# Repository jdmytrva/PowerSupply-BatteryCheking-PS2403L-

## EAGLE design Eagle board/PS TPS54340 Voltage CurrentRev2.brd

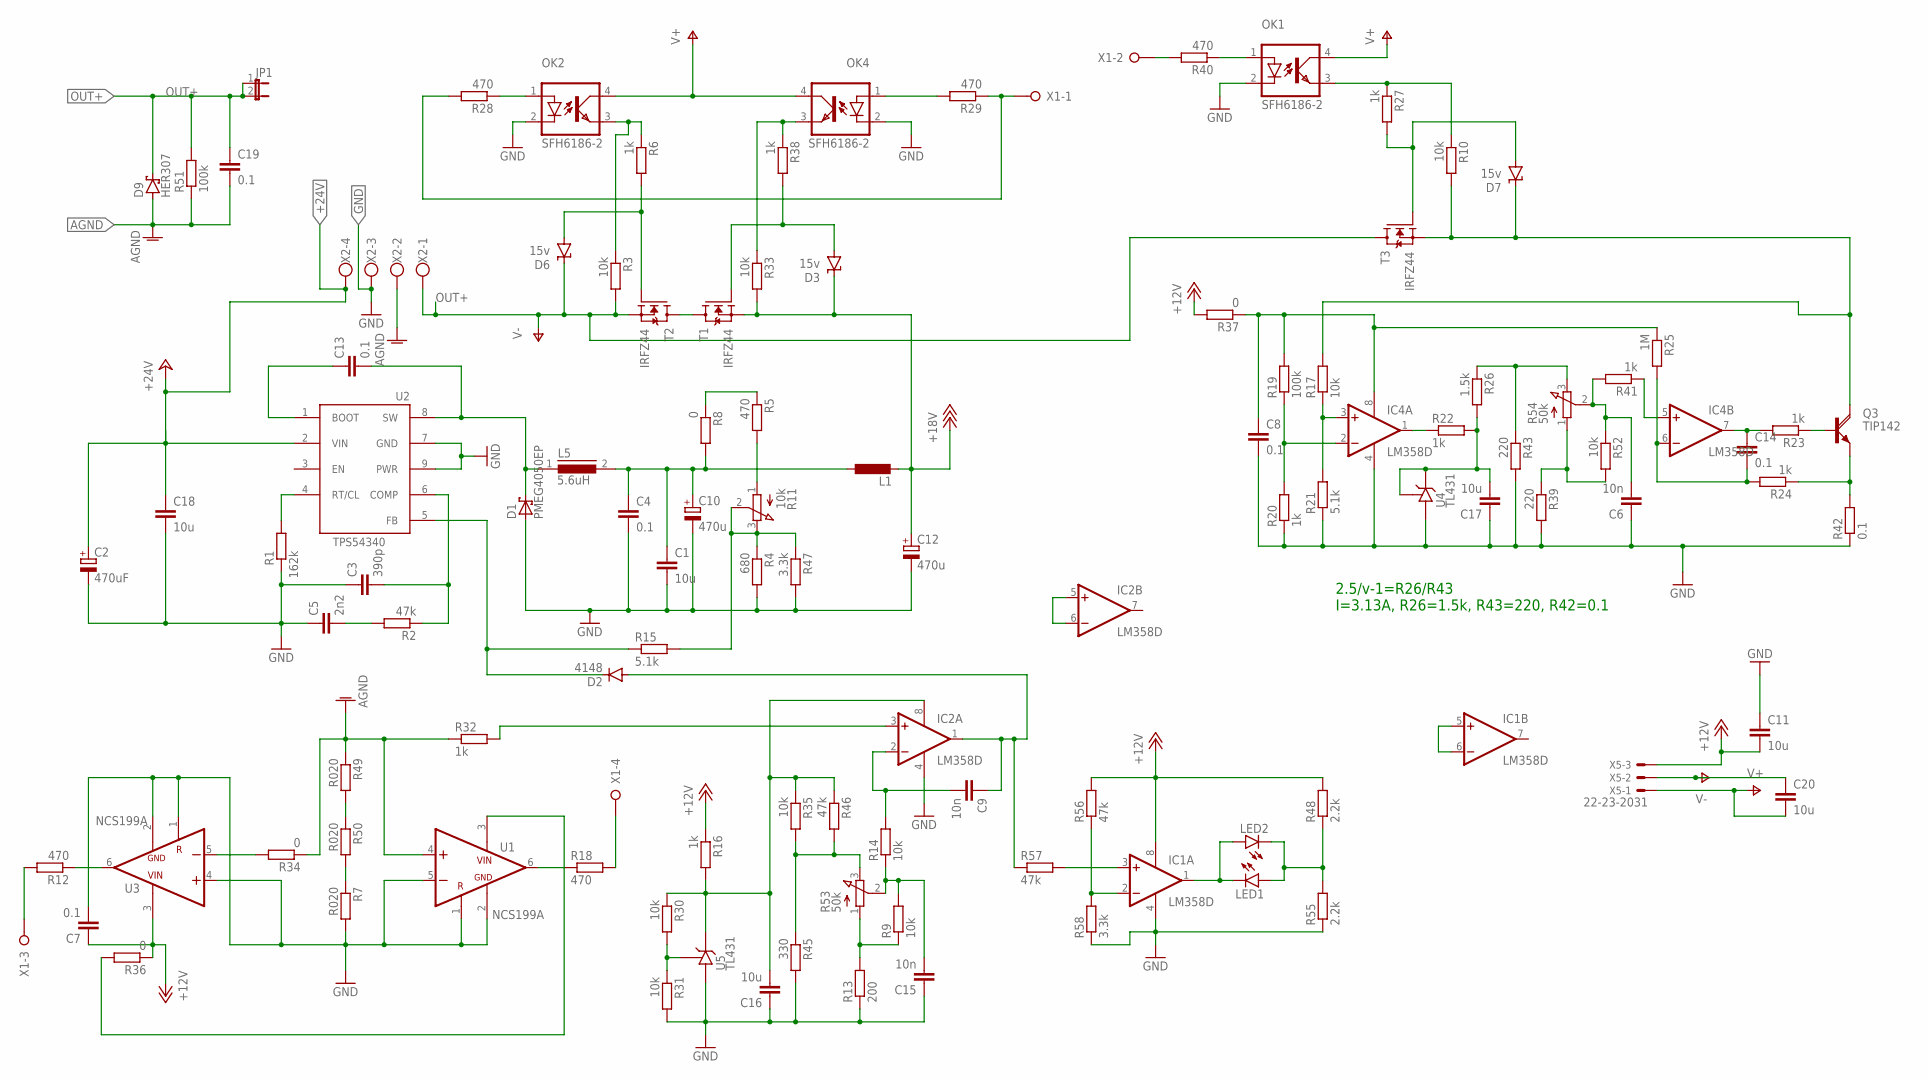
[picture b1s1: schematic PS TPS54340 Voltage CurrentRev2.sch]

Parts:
C1, C18: 10u; C1210
C2: 470uF; E5-10,5
C3: 390p; C0603K
C4, C8, C14: 0.1; C1206
C5: 2n2; C0603K
C6, C9, C15: 10n; C0603K
C7: 0.1; C0603K
C10, C12: 470u; E5-10,5
C11, C20: 10u; C1206
C13: 0.1; C102-043X133
C16, C17: 10u; C0603K
C19: 0.1; C150-054X183
D1: PMEG4050EP; SOD128
D2: 4148; SOD80C
D3, D6, D7: 15v; SMBJ
D9: HER307; CB429-17
IC1, IC2, IC4: LM358D; SO08
JP1: JP1E; JP1
L1: L-EU0207/5V; 0207/5V
L5: 5.6uH; DR125
LED1, LED2: LEDB152; Q62902-B152
OK1, OK2, OK4: SFH6186-2; SMD4-7
Q3: TIP142; SOT93
R1: 162k; R1206
R2, R46, R56, R57: 47k; R0603
R3, R9, R10, R30, R31, R33, R35, R52: 10k; R0603
R4: 680; R1206
R5: 470; R1206
R6, R16, R22, R27, R38: 1k; R0603
R7, R49, R50: R020; R1206
R8: 0; R0603
R11: 10k; 3RP/1610N
R12, R18, R28, R29, R40: 470; R0603
R13: 200; R0603
R14, R17: 10k; R1206
R15: 5.1k; R0603
R19: 100k; R1206
R20, R23, R24, R32, R41: 1k; R1206
R21: 5.1k; R1206
R25: 1M; R1206
R26: 1.5k; R0603
R34, R36, R37: 0; R1206
R39, R43: 220; R0603
R42: 0.1; 0414/15
R45: 330; R0603
R47: 3.3k; R1206
R48, R55: 2.2k; R0603
R51: 100k; 0207/15
R53, R54: 50k; 3RP/1610N
R58: 3.3k; R0603
T1, T2, T3: IRFZ44; DPAK_TO252
U1, U3: NCS199A; SOT363
U2: TPS54340; HSOP
U4, U5: TL431; SOT23
X1: W237-04P; W237-4P
X2: W237-4
X5: 22-23-2031

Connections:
+12V: C7.1, C11.2, IC1.8 (V+), R16.1, R36.1, R37.2, R48.2, R56.2, U3.3 (VCC), X5.3
+18V: C12.+, D3.C, L1.2, R33.2, T1.3 (S)
+24V: C2.+, C18.1, U2.2 (VIN), X2.4
AGND: C19.2, D9.A, R32.1, R34.1, R49.1, R51.1, U1.4 (IN+), X2.2
GND: C1.2, C2.-, C3.1, C4.2, C5.1, C6.1, C7.2, C8.2, C10.-, C11.1, C12.-, C15.1, C16.1, C17.1, C18.2, D1.2 (A), IC1.4 (V-), IC2.4 (V-), IC4.4 (V-), OK1.2 (C), OK2.2 (C), OK4.2 (C), R1.1, R4.2, R7.2, R13.1, R20.1, R21.1, R31.2, R39.2, R42.1, R43.2, R45.2, R47.2, R55.1, R58.1, U1.1 (REF), U1.2 (GND), U1.5 (IN-), U2.7 (GND), U2.9 (PWR), U3.1 (REF), U3.2 (GND), U3.4 (IN+), U4.3 (A), U5.3 (A), X2.3
unnamed: R1.2, U2.4 (RT/CL)
unnamed: C5.2, R2.2
unnamed: C3.2, R2.1, U2.6 (COMP)
unnamed: R5.2, R11.1 (A)
unnamed: D6.A, R6.2, T2.1 (G)
unnamed: IC2.3 (+IN), R32.2
unnamed: R4.1, R11.2 (S), R11.3 (E), R15.2, R47.1
unnamed: C16.2, IC2.8 (V+), R16.2, R30.1, R35.1, R46.1, U5.1 (C)
unnamed: OK2.3 (EMIT), R3.1, R6.1
unnamed: D3.A, R38.2, T1.1 (G)
unnamed: C13.1, U2.1 (BOOT)
unnamed: C13.2, D1.1 (K), L5.1, U2.8 (SW)
unnamed: R12.1, U3.6 (OUT)
unnamed: C9.2, IC2.2 (-IN), R14.2
unnamed: R30.2, R31.1, U5.2 (R)
unnamed: C9.1, D2.A, IC2.1 (OUT), R57.1
unnamed: C15.2, R9.2, R14.1, R53.2 (S)
unnamed: R34.2, U3.5 (IN-)
unnamed: D2.C, R15.1, U2.5 (FB)
unnamed: R18.1, U1.6 (OUT)
unnamed: T1.2 (D), T2.2 (D)
unnamed: IC1.1 (OUT), LED1.K (C), LED2.A
unnamed: C1.1, C4.1, C10.+, L1.1, L5.2, R8.2
unnamed: Q3.B, R23.1
unnamed: OK1.1 (A), R40.1
unnamed: C14.2, IC4.6 (-IN), R24.2, R25.2
unnamed: R26.1, R43.1, R54.3 (E)
unnamed: D7.C, Q3.C, R10.2, R17.2, T3.3 (S)
unnamed: OK1.3 (EMIT), R10.1, R27.1
unnamed: LED1.A, LED2.K (C), R48.1, R55.2
unnamed: R35.2, R45.1, R46.2, R53.3 (E)
unnamed: IC4.5 (+IN), R41.1
unnamed: IC1.2 (-IN), R56.1, R58.2
unnamed: R36.2, U1.3 (VCC)
unnamed: R18.2, X1.4
unnamed: R12.2, X1.3
unnamed: D7.A, R27.2, T3.1 (G)
unnamed: R39.1, R52.2, R54.1 (A)
unnamed: C8.1, IC4.8 (V+), R19.2, R25.1, R37.1
unnamed: R40.2, X1.2
unnamed: R9.1, R13.2, R53.1 (A)
unnamed: R49.2, R50.1
unnamed: IC2.5 (+IN), IC2.6 (-IN)
unnamed: IC1.3 (+IN), R57.2
unnamed: IC1.5 (+IN), IC1.6 (-IN)
unnamed: R7.1, R50.2
unnamed: OK4.3 (EMIT), R33.1, R38.1
unnamed: OK4.1 (A), R29.2
unnamed: R28.2, R29.1, X1.1
unnamed: OK2.1 (A), R28.1
unnamed: C17.2, R22.2, R26.2, U4.1 (C), U4.2 (R)
unnamed: R5.1, R8.1
unnamed: Q3.E, R24.1, R42.2
unnamed: C14.1, IC4.7 (OUT), R23.2
unnamed: C6.2, R41.2, R52.1, R54.2 (S)
unnamed: IC4.1 (OUT), R22.1
unnamed: IC4.3 (+IN), R17.1, R21.2
unnamed: IC4.2 (-IN), R19.1, R20.2
OUT+: C19.1, C20.1, D6.C, D9.C, JP1.1, JP1.2, R3.2, R51.2, T2.3 (S), T3.2 (D), X2.1, X5.2
V+: C20.2, OK1.4 (COL), OK2.4 (COL), OK4.4 (COL), X5.1

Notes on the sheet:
2.5/v-1=R26/R43 I=3.13A, R26=1.5k, R43=220, R42=0.1

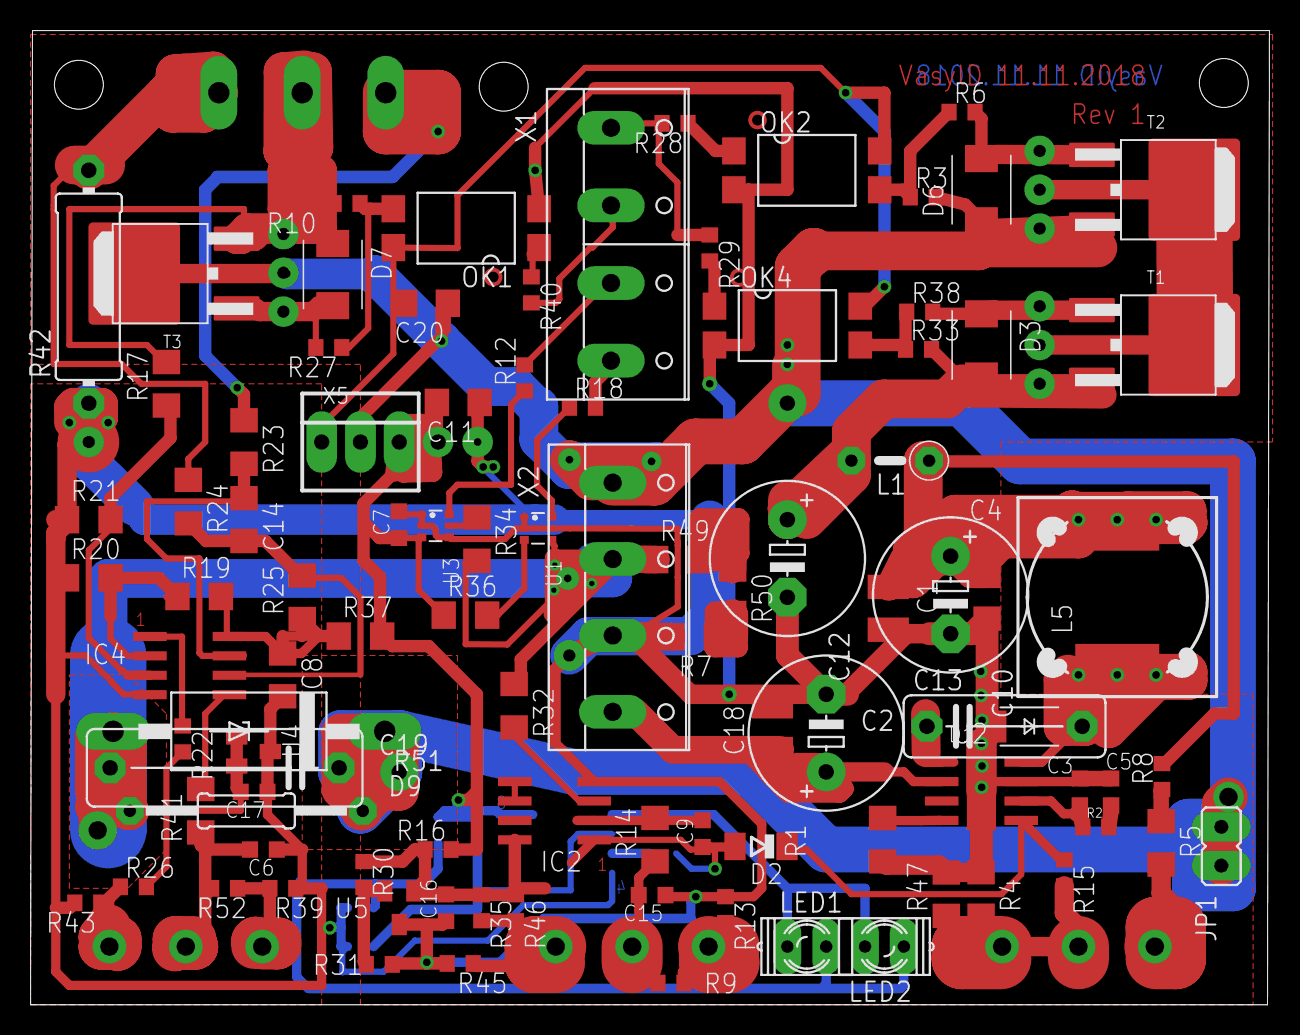
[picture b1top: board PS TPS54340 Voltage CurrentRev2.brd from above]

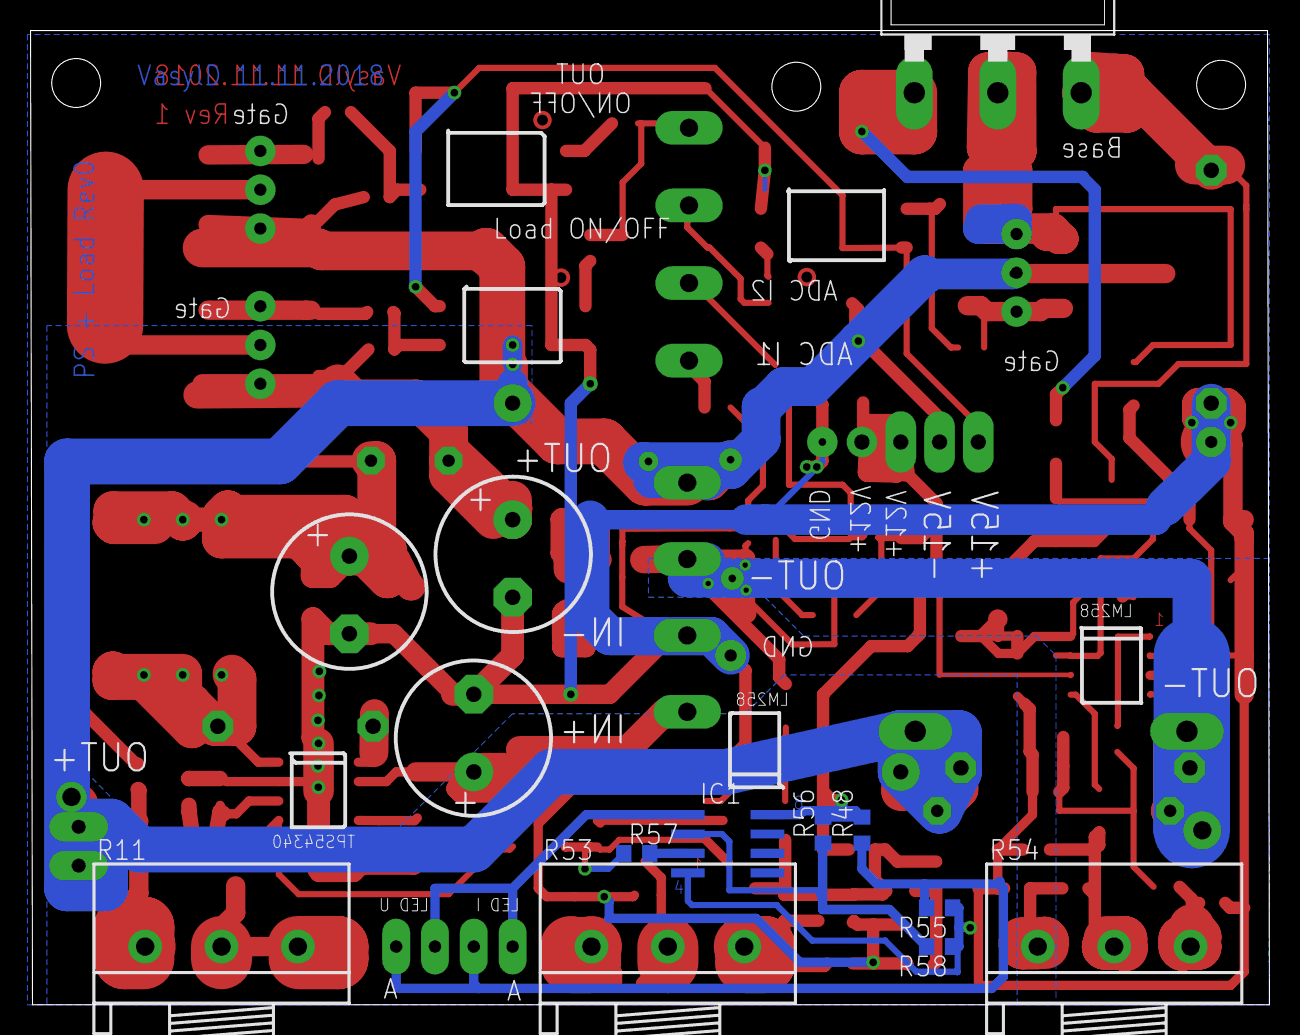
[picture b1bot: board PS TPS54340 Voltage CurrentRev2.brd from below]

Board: 2 copper layers, 81.1 x 63.8 mm, 106 parts (10 on the bottom side), 65 nets.

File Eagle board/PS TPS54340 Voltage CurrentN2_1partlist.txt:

Partlist

Exported from PS TPS54340 Voltage CurrentN2_1.sch at 15.11.2018 13:39

EAGLE Version 9.2.2 Copyright (c) 1988-2018 Autodesk, Inc.

Assembly variant: 

Part     Value          Device          Package      Library          Sheet

C1       10u            C-EUC1210       C1210        rcl              1
C2       470uF          CPOL-EUE5-10.5  E5-10,5      rcl              1
C3       47p            C-EUC0603K      C0603K       rcl              1
C4       0.1            C-EUC1206       C1206        rcl              1
C5       1n             C-EUC0603K      C0603K       rcl              1
C6       0.1            C-EUC0603K      C0603K       rcl              1
C7       0.1            C-EUC0603K      C0603K       rcl              1
C8       0.1            C-EUC1206       C1206        rcl              1
C9       10n            C-EUC0603K      C0603K       rcl              1
C10      470u           CPOL-EUE5-10.5  E5-10,5      rcl              1
C11      0.1            C-EUC1206       C1206        rcl              1
C12      470u           CPOL-EUE5-10.5  E5-10,5      rcl              1
C13      0.1            C-EU102-043X133 C102-043X133 rcl              1
C14      0.1            C-EUC1206       C1206        rcl              1
C15      0.1            C-EUC0603K      C0603K       rcl              1
C16      10u            C-EUC0603K      C0603K       rcl              1
C17      10u            C-EUC0603K      C0603K       rcl              1
C18      10u            C-EUC1210       C1210        rcl              1
C19      0.1            C-EU150-054X183 C150-054X183 rcl              1
C20      0.1            C-EUC1206       C1206        rcl              1
D1       PMEG4050EP     PMEG4050EP      SOD128       NXP_60_26022015  1
D2       4148           PMLL41SOD80C    SOD80C       diode            1
D3       15v            SUPPRESSOR-SMBJ SMBJ         diode            1
D6       15v            SUPPRESSOR-SMBJ SMBJ         diode            1
D7       15v            SUPPRESSOR-SMBJ SMBJ         diode            1
D9       HER307         15KEXX          CB429-17     diode            1
IC1      LM358D         LM358D          SO08         linear           1
IC2      LM358D         LM358D          SO08         linear           1
IC4      LM358D         LM358D          SO08         linear           1
JP1                     JP1E            JP1          jumper           1
L1                      L-EU0207/5V     0207/5V      rcl              1
L5       5.6uH          DR125           DR125        inductors        1
LED1                    LEDB152         Q62902-B152  led              1
LED2                    LEDB152         Q62902-B152  led              1
OK1      SFH6186-2      SFH6186-2       SMD4-7       optocoupler      1
OK2      SFH6186-2      SFH6186-2       SMD4-7       optocoupler      1
OK4      SFH6186-2      SFH6186-2       SMD4-7       optocoupler      1
Q3       TIP142         TIP142          SOT93        transistor-power 1
R1       150k           R-EU_R1206      R1206        rcl              1
R2       47k            R-EU_R0603      R0603        rcl              1
R3       10k            R-EU_R0603      R0603        rcl              1
R4       470            R-EU_R1206      R1206        rcl              1
R5       470            R-EU_R1206      R1206        rcl              1
R6       1k             R-EU_R0603      R0603        rcl              1
R7       R020           R-EU_R1206      R1206        rcl              1
R8       x              R-EU_R0603      R0603        rcl              1
R9       10k            R-EU_R0603      R0603        rcl              1
R10      10k            R-EU_R0603      R0603        rcl              1
R11      10k            3RP/1610N       3RP/1610N    pot              1
R12      1k             R-EU_R0603      R0603        rcl              1
R13      200            R-EU_R0603      R0603        rcl              1
R14      10k            R-EU_R1206      R1206        rcl              1
R15      5.1k           R-EU_R0603      R0603        rcl              1
R16      1k             R-EU_R0603      R0603        rcl              1
R17      10k            R-EU_R1206      R1206        rcl              1
R18      1k             R-EU_R0603      R0603        rcl              1
R19      100k           R-EU_R1206      R1206        rcl              1
R20      1k             R-EU_R1206      R1206        rcl              1
R21      5.1k           R-EU_R1206      R1206        rcl              1
R22      1k             R-EU_R0603      R0603        rcl              1
R23      1k             R-EU_R1206      R1206        rcl              1
R24      1k             R-EU_R1206      R1206        rcl              1
R25      1M             R-EU_R1206      R1206        rcl              1
R26      1.5k           R-EU_R0603      R0603        rcl              1
R27      1k             R-EU_R0603      R0603        rcl              1
R28      470            R-EU_R0603      R0603        rcl              1
R29      470            R-EU_R0603      R0603        rcl              1
R30      10k            R-EU_R0603      R0603        rcl              1
R31      10k            R-EU_R0603      R0603        rcl              1
R32      1k             R-EU_R1206      R1206        rcl              1
R33      10k            R-EU_R0603      R0603        rcl              1
R34      0              R-EU_R1206      R1206        rcl              1
R35      10k            R-EU_R0603      R0603        rcl              1
R36      0              R-EU_R1206      R1206        rcl              1
R37      0              R-EU_R1206      R1206        rcl              1
R38      1k             R-EU_R0603      R0603        rcl              1
R39      220            R-EU_R0603      R0603        rcl              1
R40      470            R-EU_R0603      R0603        rcl              1
R41      1k             R-EU_R1206      R1206        rcl              1
R42      0.1            R-EU_0414/15    0414/15      rcl              1
R43      220            R-EU_R0603      R0603        rcl              1
R44      2.2k           R-EU_R0603      R0603        rcl              1
R45      330            R-EU_R0603      R0603        rcl              1
R46      x              R-EU_R0603      R0603        rcl              1
R47      3.3k           R-EU_R1206      R1206        rcl              1
R48      2.2k           R-EU_R0603      R0603        rcl              1
R49      R020           R-EU_R1206      R1206        rcl              1
R50      R020           R-EU_R1206      R1206        rcl              1
R51      100k           R-EU_0207/15    0207/15      rcl              1
R52      10k            R-EU_R0603      R0603        rcl              1
R53      50k            3RP/1610N       3RP/1610N    pot              1
R54      50k            3RP/1610N       3RP/1610N    pot              1
R55      2.2k           R-EU_R0603      R0603        rcl              1
R56      47k            R-EU_R0603      R0603        rcl              1
R57      47k            R-EU_R0603      R0603        rcl              1
R58      3.3k           R-EU_R0603      R0603        rcl              1
T1       IRFZ44         MOSFET-N-DPAK   DPAK_TO252   we-transistor    1
T2       IRFZ44         MOSFET-N-DPAK   DPAK_TO252   we-transistor    1
T3       IRFZ44         MOSFET-N-DPAK   DPAK_TO252   we-transistor    1
U1       NCS199A        NCS199A         SOT363       ProjectLibrary   1
U2       TPS54340       TPS54340SO8     HSOP         ProjectLibrary   1
U3       NCS199A        NCS199A         SOT363       ProjectLibrary   1
U4       TL431          TL431           SOT23        1my              1
U5       TL431          TL431           SOT23        1my              1
X1                      W237-04P        W237-4P      con-wago-508     1
X2                      W237-4          W237-4       con-wago-500     1
X5       22-23-2031     22-23-2031      22-23-2031   con-molex        1

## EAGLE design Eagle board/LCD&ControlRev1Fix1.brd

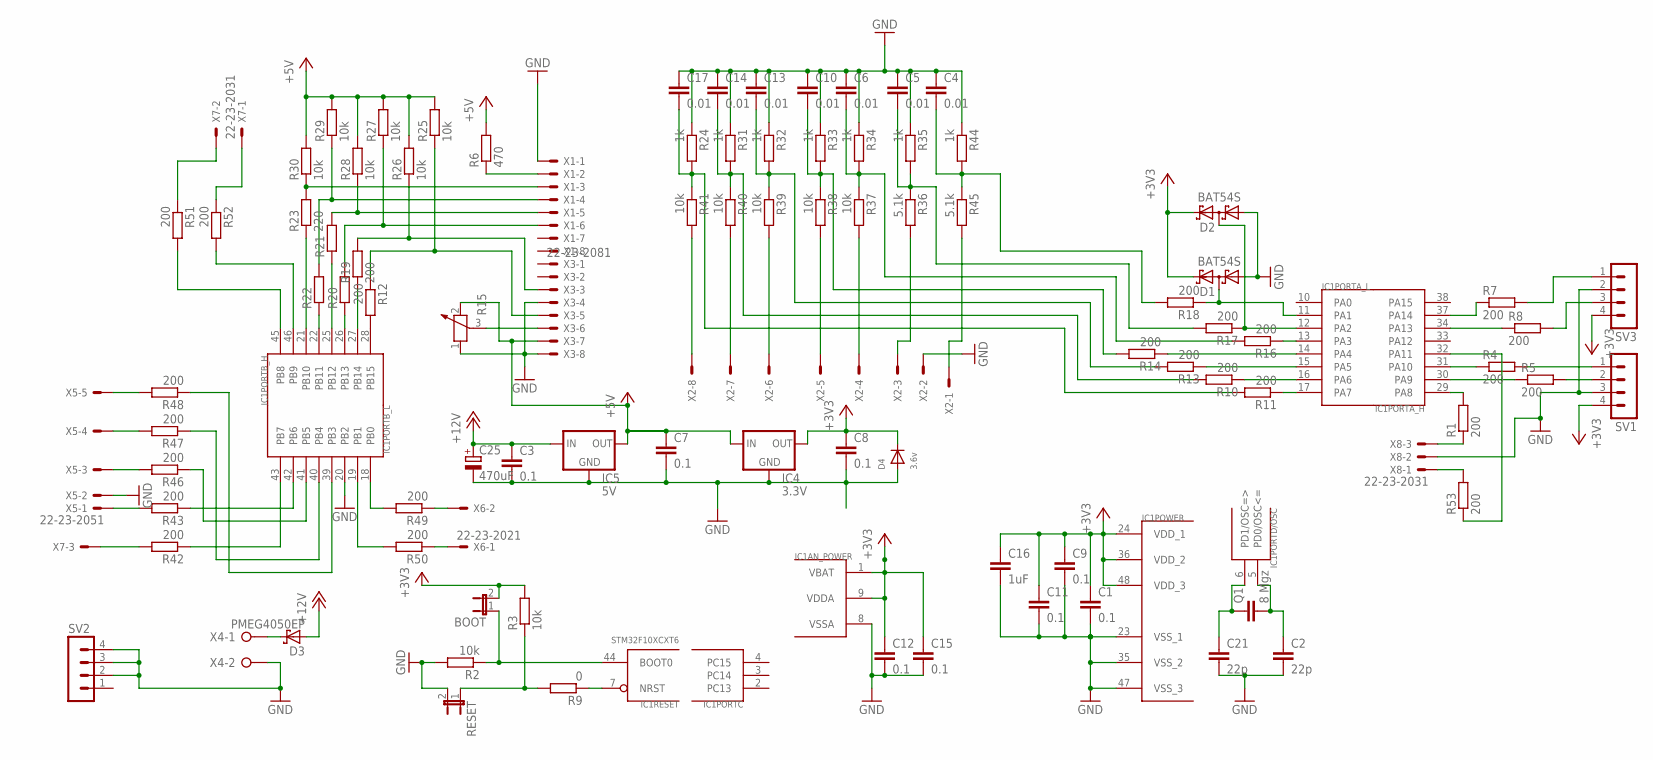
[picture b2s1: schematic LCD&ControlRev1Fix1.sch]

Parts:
BOOT: JP1E; JP1
C1, C9, C11, C12, C15: 0.1; C0402
C2, C21: 22p; C0603
C3, C7, C8: 0.1; C1206
C4, C5, C6, C10, C13, C14, C17: 0.01; C0603
C16: 1uF; C0603
C25: 470uF; E5-10,5
D1, D2: BAT54S; SOT23
D3: PMEG4050EP; SOD128
D4: 3.6v; SOD-123
IC1: STM32F10XCXT6; TQFP48
IC4: 3.3V; SOT223
IC5: 5V; SOT223
Q1: 8 Mgz; C050-024X044
R1, R4, R5, R7, R8, R10, R11, R13, R14, R16, R17, R18, R19, R42, R43, R46, R47, R48, R49, R50, R51, R52, R53: 200; R0603
R2, R25, R26, R27, R28, R29, R30, R37, R38, R39, R40, R41: 10k; R0603
R3: 10k; M1206
R6: 470; R0603
R9: 0; M1206
R12: 200; M1206
R15: POTENTIOMETER_PT-10S; PT-10S
R20, R21, R22: R-EU_R0603; R0603
R23: 220; R0603
R24, R31, R32, R33, R34, R35, R44: 1k; R0603
R36, R45: 5.1k; R0603
RESET: JP1E; JP1
SV1, SV2, SV3: MA04-1
X1, X2, X3: 22-23-2081
X4: W237-02P; W237-132
X5: 22-23-2051
X6: 22-23-2021
X7, X8: 22-23-2031

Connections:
+3V3: BOOT.2, C1.1, C8.1, C9.1, C11.1, C12.1, C15.1, C16.1, D1.2 (C2), D2.2 (C2), D4.C, IC1.1 (VBAT), IC1.9 (VDDA), IC1.24 (VDD_1), IC1.36 (VDD_2), IC1.48 (VDD_3), IC4.2 (OUT), IC4.4 (OUT), R3.2, SV1.4, SV3.4
+5V: C7.1, IC4.3 (IN), IC5.2 (OUT), IC5.4 (OUT), R6.2, R15.2, R25.2, R26.2, R27.2, R28.2, R29.2, R30.2, X3.7
+12V: C3.1, C25.+, D3.2 (A), IC5.3 (IN)
GND: C1.2, C2.2, C3.2, C4.1, C5.1, C6.1, C7.2, C8.2, C9.2, C10.1, C11.2, C12.2, C13.1, C14.1, C15.2, C16.2, C17.1, C21.2, C25.-, D1.1 (A1), D2.1 (A1), D4.A, IC1.8 (VSSA), IC1.20 (PB2), IC1.23 (VSS_1), IC1.35 (VSS_2), IC1.47 (VSS_3), IC4.1 (GND), IC5.1 (GND), R2.2, R15.1, R24.1, R31.1, R32.1, R33.1, R34.1, R35.1, R44.1, RESET.2, SV1.3, SV2.2, SV2.3, SV2.4, SV3.2, X1.1, X2.2, X3.4, X3.8, X4.2, X5.2, X8.2
unnamed: IC1.29 (PA8), R1.2
unnamed: C21.1, IC1.6 (PD1/OSC=>), Q1.1
unnamed: C2.1, IC1.5 (PD0/OSC<=), Q1.2
unnamed: IC1.37 (PA14), R7.1
unnamed: IC1.34 (PA13), R8.1
unnamed: R7.2, SV3.1
unnamed: R3.1, R9.2, RESET.1
unnamed: IC1.7 (NRST), R9.1
unnamed: IC1.31 (PA10), R4.1
unnamed: IC1.30 (PA9), R5.1
unnamed: R4.2, SV1.1
unnamed: R6.1, X1.2
unnamed: R15.3, X3.6
unnamed: D3.1 (K), X4.1
unnamed: R22.2, R29.1, X1.4
unnamed: C17.2, R11.2, R24.2, R41.1
unnamed: R52.1, X7.1
unnamed: R1.1, X8.3
unnamed: IC1.46 (PB9), R52.2
unnamed: R43.2, X5.1
unnamed: R21.2, R28.1, X1.5
unnamed: D1.3 (C1A2), IC1.11 (PA1), R18.1
unnamed: R20.2, R27.1, X1.6
unnamed: R19.2, R26.1, X3.3
unnamed: R23.2, R30.1, X1.3
unnamed: R12.1, R25.1, X3.5
unnamed: IC1.21 (PB10), R23.1
unnamed: IC1.22 (PB11), R22.1
unnamed: IC1.25 (PB12), R21.1
unnamed: IC1.45 (PB8), R51.2
unnamed: R47.2, X5.4
unnamed: R5.2, SV1.2
unnamed: R46.2, X5.3
unnamed: R48.2, X5.5
unnamed: R51.1, X7.2
unnamed: R8.2, SV3.3
unnamed: IC1.18 (PB0), R49.2
unnamed: IC1.43 (PB7), R42.1
unnamed: D2.3 (C1A2), IC1.12 (PA2), R17.1
unnamed: BOOT.1, IC1.44 (BOOT0), R2.1
unnamed: R42.2, X7.3
unnamed: IC1.42 (PB6), R43.1
unnamed: C14.2, R10.2, R31.2, R40.1
unnamed: C13.2, R13.2, R32.2, R39.1
unnamed: R38.2, X2.5
unnamed: IC1.13 (PA3), R16.1
unnamed: IC1.19 (PB1), R50.2
unnamed: IC1.14 (PA4), R14.1
unnamed: C6.2, R16.2, R34.2, R37.1
unnamed: C5.2, R17.2, R35.2, R36.1
unnamed: IC1.26 (PB13), R20.1
unnamed: IC1.27 (PB14), R19.1
unnamed: IC1.28 (PB15), R12.2
unnamed: R49.1, X6.2
unnamed: IC1.15 (PA5), R13.1
unnamed: IC1.16 (PA6), R10.1
unnamed: R45.2, X2.1
unnamed: IC1.41 (PB5), R46.1
unnamed: IC1.17 (PA7), R11.1
unnamed: R50.1, X6.1
unnamed: IC1.40 (PB4), R47.1
unnamed: IC1.39 (PB3), R48.1
unnamed: C4.2, R18.2, R44.2, R45.1
unnamed: R36.2, X2.3
unnamed: R37.2, X2.4
unnamed: R53.2, X8.1
unnamed: IC1.32 (PA11), R53.1
unnamed: C10.2, R14.2, R33.2, R38.1
unnamed: R39.2, X2.6
unnamed: R40.2, X2.7
unnamed: R41.2, X2.8

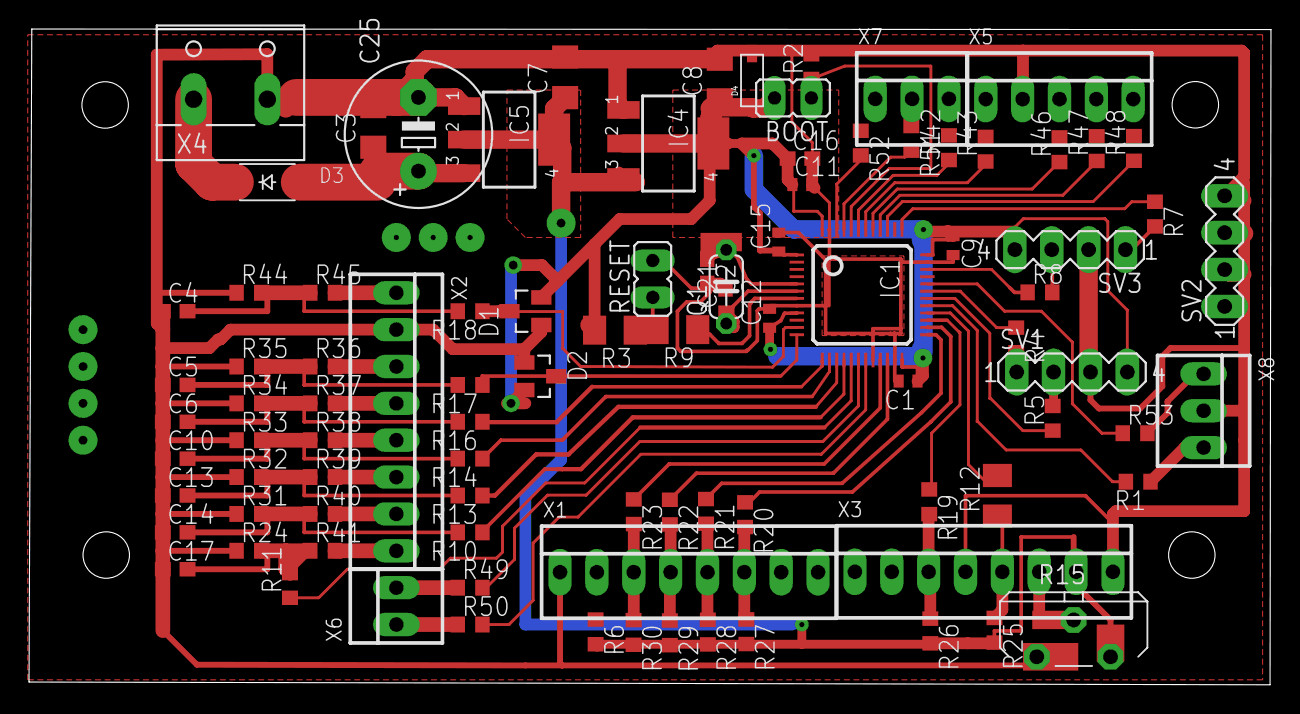
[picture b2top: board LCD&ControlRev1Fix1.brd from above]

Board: 2 copper layers, 85.6 x 45.2 mm, 93 parts (0 on the bottom side), 75 nets.

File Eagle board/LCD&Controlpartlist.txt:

Partlist

Exported from LCD&Control2jlcpcb.sch at 15.11.2018 13:36

EAGLE Version 9.2.2 Copyright (c) 1988-2018 Autodesk, Inc.

Assembly variant: 

Part     Value          Device               Package      Library      Sheet

BOOT                    JP1E                 JP1          jumper       1
C1       0.1            C-EUC0402            C0402        rcl          1
C2       22p            C-EUC0603            C0603        rcl          1
C3       0.1            C-EUC1206            C1206        rcl          1
C4       0.01           C-EUC0603            C0603        rcl          1
C5       0.01           C-EUC0603            C0603        rcl          1
C6       0.01           C-EUC0603            C0603        rcl          1
C7       0.1            C-EUC1206            C1206        rcl          1
C8       0.1            C-EUC1206            C1206        rcl          1
C9       0.1            C-EUC0402            C0402        rcl          1
C10      0.01           C-EUC0603            C0603        rcl          1
C11      0.1            C-EUC0402            C0402        rcl          1
C12      0.1            C-EUC0402            C0402        rcl          1
C13      0.01           C-EUC0603            C0603        rcl          1
C14      0.01           C-EUC0603            C0603        rcl          1
C15      0.1            C-EUC0402            C0402        rcl          1
C16      1uF            C-EUC0603            C0603        rcl          1
C17      0.01           C-EUC0603            C0603        rcl          1
C21      22p            C-EUC0603            C0603        rcl          1
C25      470uF          CPOL-EUE5-10.5       E5-10,5      rcl          1
D1       BAT54S         BAT54S               SOT23        diode        1
D2       BAT54S         BAT54S               SOT23        diode        1
D3       PMEG4050EP     PMEG4050EP           SOD128       nxp_60       1
D4       3.6v           DIODESOD-123         SOD-123      adafruit     1
IC1      STM32F10XCXT6  STM32F10XCXT6        TQFP48       stm32(1)     1
IC4      3.3V           LM1117               SOT223       v-reg-2      1
IC5      5V             LM1117               SOT223       v-reg-2      1
Q1       8  Mgz         C-EU050-024X044      C050-024X044 rcl          1
R1       200            R-EU_R0603           R0603        rcl          1
R2       10k            R-EU_R0603           R0603        rcl          1
R3       10k            R-EU_M1206           M1206        rcl          1
R4       200            R-EU_R0603           R0603        rcl          1
R5       200            R-EU_R0603           R0603        rcl          1
R6       470            R-EU_R0603           R0603        rcl          1
R7       200            R-EU_R0603           R0603        rcl          1
R8       200            R-EU_R0603           R0603        rcl          1
R9       0              R-EU_M1206           M1206        rcl          1
R10      200            R-EU_R0603           R0603        rcl          1
R11      200            R-EU_R0603           R0603        rcl          1
R12      200            R-EU_M1206           M1206        rcl          1
R13      200            R-EU_R0603           R0603        rcl          1
R14      200            R-EU_R0603           R0603        rcl          1
R15                     POTENTIOMETER_PT-10S PT-10S       rcl          1
R16      200            R-EU_R0603           R0603        rcl          1
R17      200            R-EU_R0603           R0603        rcl          1
R18      200            R-EU_R0603           R0603        rcl          1
R19      200            R-EU_R0603           R0603        rcl          1
R20                     R-EU_R0603           R0603        rcl          1
R21                     R-EU_R0603           R0603        rcl          1
R22                     R-EU_R0603           R0603        rcl          1
R23      220            R-EU_R0603           R0603        rcl          1
R24      1k             R-EU_R0603           R0603        rcl          1
R25      10k            R-EU_R0603           R0603        rcl          1
R26      10k            R-EU_R0603           R0603        rcl          1
R27      10k            R-EU_R0603           R0603        rcl          1
R28      10k            R-EU_R0603           R0603        rcl          1
R29      10k            R-EU_R0603           R0603        rcl          1
R30      10k            R-EU_R0603           R0603        rcl          1
R31      1k             R-EU_R0603           R0603        rcl          1
R32      1k             R-EU_R0603           R0603        rcl          1
R33      1k             R-EU_R0603           R0603        rcl          1
R34      1k             R-EU_R0603           R0603        rcl          1
R35      1k             R-EU_R0603           R0603        rcl          1
R36      5.1k           R-EU_R0603           R0603        rcl          1
R37      10k            R-EU_R0603           R0603        rcl          1
R38      10k            R-EU_R0603           R0603        rcl          1
R39      10k            R-EU_R0603           R0603        rcl          1
R40      10k            R-EU_R0603           R0603        rcl          1
R41      10k            R-EU_R0603           R0603        rcl          1
R42      200            R-EU_R0603           R0603        rcl          1
R43      200            R-EU_R0603           R0603        rcl          1
R44      1k             R-EU_R0603           R0603        rcl          1
R45      5.1k           R-EU_R0603           R0603        rcl          1
R46      200            R-EU_R0603           R0603        rcl          1
R47      200            R-EU_R0603           R0603        rcl          1
R48      200            R-EU_R0603           R0603        rcl          1
R49      200            R-EU_R0603           R0603        rcl          1
R50      200            R-EU_R0603           R0603        rcl          1
R51      200            R-EU_R0603           R0603        rcl          1
R52      200            R-EU_R0603           R0603        rcl          1
R53      200            R-EU_R0603           R0603        rcl          1
RESET                   JP1E                 JP1          jumper       1
SV1                     MA04-1               MA04-1       con-lstb     1
SV2                     MA04-1               MA04-1       con-lstb     1
SV3                     MA04-1               MA04-1       con-lstb     1
X1       22-23-2081     22-23-2081           22-23-2081   con-molex    1
X2       22-23-2081     22-23-2081           22-23-2081   con-molex    1
X3       22-23-2081     22-23-2081           22-23-2081   con-molex    1
X4                      W237-02P             W237-132     con-wago-508 1
X5       22-23-2051     22-23-2051           22-23-2051   con-molex    1
X6       22-23-2021     22-23-2021           22-23-2021   con-molex    1
X7       22-23-2031     22-23-2031           22-23-2031   con-molex    1
X8       22-23-2031     22-23-2031           22-23-2031   con-molex    1

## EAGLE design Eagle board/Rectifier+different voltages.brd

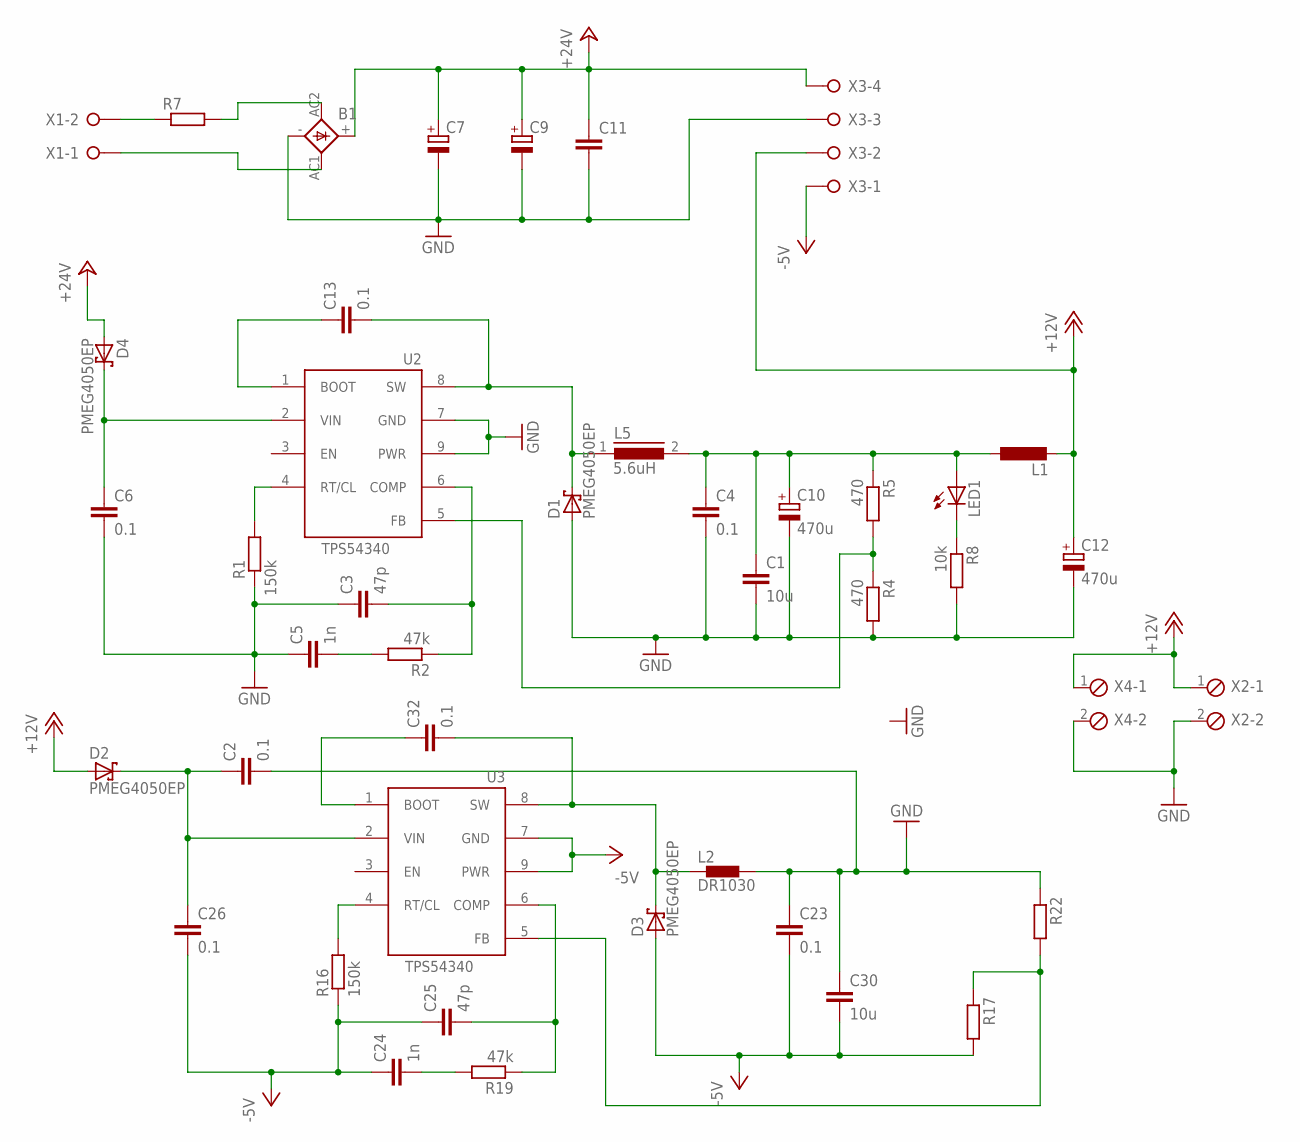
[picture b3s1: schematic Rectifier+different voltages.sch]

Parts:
B1: KBL
C1, C30: 10u; C1206
C2, C26: 0.1; C1210
C3, C25: 47p; C0603K
C4, C6, C23: 0.1; C1206
C5, C24: 1n; C0603K
C7, C9: CPOL-EUE7.5-18; E7,5-18
C10, C12: 470u; E5-10,5
C11: C-EUC1206; C1206
C13: 0.1; C102-043X133
C32: 0.1; C075-032X103
D1, D2, D3, D4: PMEG4050EP; SOD128
L1: L-EU0207/5V; 0207/5V
L2: DR1030
L5: 5.6uH; DR125
LED1: LEDB152; Q62902-B152
R1, R16: 150k; R1206
R2, R19: 47k; R0603
R4, R5: 470; R1206
R7: R-EU_0207/10; 0207/10
R8: 10k; R0603
R17, R22: R-EU_R1206; R1206
U2: TPS54340; HSOP
U3: TPS54340SO8; HSOP
X1: W237-02P; W237-132
X2, X4: MPT2; 2POL254
X3: W237-04P; W237-4P

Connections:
+12V: C12.+, D2.2 (A), L1.2, X2.1, X3.2, X4.1
+24V: B1.+, C7.+, C9.+, C11.1, D4.2 (A), X3.4
-5V: C23.2, C24.1, C25.1, C26.2, C30.2, D3.2 (A), R16.1, R17.2, U3.7 (GND), U3.9 (PWR), X3.1
GND: B1.-, C1.2, C2.2, C3.1, C4.2, C5.1, C6.2, C7.-, C9.-, C10.-, C11.2, C12.-, C23.1, C30.1, D1.2 (A), L2.2, R1.1, R4.2, R8.2, R22.1, U2.7 (GND), U2.9 (PWR), X2.2, X3.3, X4.2
unnamed: R1.2, U2.4 (RT/CL)
unnamed: C5.2, R2.2
unnamed: C3.2, R2.1, U2.6 (COMP)
unnamed: R7.1, X1.2
unnamed: R4.1, R5.2, U2.5 (FB)
unnamed: LED1.K (C), R8.1
unnamed: C2.1, C26.1, D2.1 (K), U3.2 (VIN)
unnamed: C6.1, D4.1 (K), U2.2 (VIN)
unnamed: C13.1, U2.1 (BOOT)
unnamed: C13.2, D1.1 (K), L5.1, U2.8 (SW)
unnamed: B1.AC1 (AC2), X1.1
unnamed: B1.AC2 (AC1), R7.2
unnamed: R17.1, R22.2, U3.5 (FB)
unnamed: R16.2, U3.4 (RT/CL)
unnamed: C25.2, R19.1, U3.6 (COMP)
unnamed: C1.1, C4.1, C10.+, L1.1, L5.2, LED1.A, R5.1
unnamed: C32.1, U3.1 (BOOT)
unnamed: C32.2, D3.1 (K), L2.1, U3.8 (SW)
unnamed: C24.2, R19.2

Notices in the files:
parts and their libraries:
NXP_60_26022015: This library may be distributed and adapted freely for any purpose, as long as NXP is credited and any new creation is licensed under the same terms.
